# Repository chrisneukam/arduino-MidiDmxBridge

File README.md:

# Arduino Project: MIDI-DMX Bridge

The `MIDI-DMX Bridge` is an Arduino-based hardware and software solution that converts MIDI Continuous Controller signals to DMX commands. The project consists of a hardware schematic and PCB designed using KiCad, an Arduino sketch, and an Arduino library. It can be used to control DMX fixtures such as lights, fog machines, and more.

## Lightning Fixture Compatibility

The `MIDI-DMX Bridge` Arduino project is designed to seamlessly integrate with the lighting fixtures *Stairville CLB4 RGB Compact LED Bar 4* and two *Stairville LED Flood Panel 150*. Here's how the bridge supports these fixtures:

1. **Stairville CLB4 RGB Compact LED Bar 4**:
    - This LED bar operates in the 14-channel DMX mode, the start address 1.
    - Each of its four individual LED spots can be controlled independently using the MIDI-DMX Bridge.
    - Adjust colors, intensity, and effects with precision.
    - Perfect for creating dynamic lighting displays in various settings.

2. **Stairville LED Flood Panel 150**:
    - The LED Flood Panel operates in the 4-channel DMX mode, the start addresses are 15 and 19.
    - Use the MIDI-DMX Bridge to orchestrate its 150 LEDs for wide-area illumination.
    - Whether it’s stage lighting, architectural displays, or events, this panel delivers impressive results.

Remember to consult the user manuals for both fixtures to configure the MIDI-DMX Bridge effectively. Enjoy your creative lighting setups! 🌟

## Hardware Schematic

The hardware schematic for this project was designed using KiCad. The schematic includes the following components:

- **MIDI Input**: This component receives MIDI Continuous Controller signals on a defined MIDI channel from an external device.
- **Arduino Board**: This component processes the incoming MIDI signals and generates DMX commands.
- **DMX Output**: This component sends DMX commands to an external DMX device.
- **Potentiometer**: This component allows the user to adjust the intensity of the DMX signal.
- **Hardware Switch**: This component allows the user to select either a predefined DMX scene or the MIDI controlled dynamic scene.

The DMX circuit is based on the `DMX shield` from Matthias Hertel, see [DMX Shield for Arduino with isolation](https://www.mathertel.de/Arduino/DMXShield.aspx).

## PCB Design of the MIDI-DMX Bridge

The hardware design focuses on efficiency and space-saving. The compact printed circuit board (PCB) houses all essential components, including the Arduino ProMini microcontroller, MIDI interface, and DMX driver.

The PCB has the following features:

- A MIDI input jack that accepts standard 5-pin DIN connectors
- A MIDI through jack that accepts standard 5-pin DIN connectors
- A DMX output jack that supports both 3-pin XLR connectors
- A power jack that provides 9V DC power
- A Switch that selects between two DMX modes: static and dynamic scene
- A potentiometer that adjusts the DMX signal strength

The PCB layout and the circuit diagram as a 3D simulation, before and after final assembly, are shown below:

The PCB can be ordered from any PCB manufacturer that supports the KiCad format. Alternatively, the [Interactive BOM](./kicad/bom/ibom.html) tool can help with the assembly of the PCB.

The PCB shown was manufactured by [JLCPCB](https://jlcpcb.com/), the production data can be found in [kicad\production](./kicad/production) as a reference.

## Arduino Sketch

The Arduino sketch for this project is responsible for processing the incoming MIDI signals and generating DMX commands. The sketch uses its own implementation to receive MIDI signals and the [DMXSerial Library](https://github.com/mathertel/DMXSerial) to send DMX commands.

```c++
#include <DMXSerial.h>
#include <MidiDmxBridge.h>

static void onDmxChange(const uint8_t channel, const uint8_t value) {
  DMXSerial.write(channel, value);
}

static SerialReaderDefault reader;
static MidiDmxBridge MDXBridge(kMidiChannel, onDmxChange, reader);

void setup() {
  DMXSerial.init(DMXController);
  MDXBridge.begin();
}

void loop() {
  MDXBridge.setAttenuation(analogRead(kSensorPin));
  MDXBridge.listen();
}
```

For the complete Arduino sketch, please refer to [arduino-MidiDmxBridge.ino](./src/arduino-MidiDmxBridge/arduino-MidiDmxBridge.ino).

## Arduino Library

The Arduino library for this project is a custom library that provides additional functionality for processing MIDI signals and generating DMX commands. It is also available as [MidiDmxBridge](https://reference.arduino.cc/reference/en/libraries/mididmxbridge/) via the [Arduino Library manager](https://docs.arduino.cc/software/ide-v1/tutorials/installing-libraries/).
The library includes the following functions:

- `void begin()`: This function processes initializes the library.
- `void setStaticScene(const DmxRgbChannels& channels, const DmxRgb& rgb)`: This function defines the DMX static scene
- `void setAttenuation(const uint16_t attenuation)`: This function switches to the MIDI controlled dynamic scene.
- `void switchToDynamicScene()`: This function sets the attenuation of the generated DMX signal.
- `void switchToStaticScene()`: This function switches to the predefined static scene.
- `void listen()`: This function listens on the serial interface for the next MIDI CC value and updates the DMX state.

```c++
class MidiDmxBridge {
public:
  MidiDmxBridge(const uint8_t channel, DmxOnChangeCallback callback, ISerialReader& serial);
  void begin();
  void setStaticScene(const DmxRgbChannels& channels, const DmxRgb& rgb);
  void setAttenuation(const uint16_t attenuation);
  void switchToDynamicScene();
  void switchToStaticScene();
  void listen();
};
```

For the complete API, please refer to [MidiDmxBridge.h](./src/arduino-library/MidiDmxBridge/src/MidiDmxBridge.h).

### C++ Library development

The Arduino library is developed in C++ and uses CMake for configuration. The library is tested using gtest and documented using Doxygen.

```shell
cmake -S ./src/arduino-library/ -B ./build
cmake --build ./build
ctest --test-dir ./build/
```

On Linux OS code coverage using lcov and gcov is available:

```shell
cmake -DENABLE_COVERAGE=ON -S ./src/arduino-library/ -B ./build
cmake --build ./build
ctest --test-dir ./build/
cmake --build ./build --target coverage
```

The software documentation can then be accessed at [./build/html/index.html](./build/html/index.html), the code coverage results at [./build/coverage/index.html](./build/coverage/index.html).

## How to Run Codespell

To run [codespell](https://github.com/codespell-project/codespell), you need to have Python 3 installed on your system. You can install Python 3 from the official website: https://www.python.org/downloads/.

Once you have Python 3 installed, you can install [codespell](https://github.com/codespell-project/codespell) using pip, the Python package manager. Open a terminal or command prompt and type the following command:

```bash
pip install codespell
```

This will install [codespell](https://github.com/codespell-project/codespell) and all its dependencies.

To run [codespell](https://github.com/codespell-project/codespell), navigate to the root directory of your project in the terminal or command prompt and type the following command:

```bash
codespell
```

This will run [codespell](https://github.com/codespell-project/codespell) on all the files in the current directory and its subdirectories. [codespell](https://github.com/codespell-project/codespell) will check for common misspellings and suggest corrections. You can use the `-w` option to write the changes directly to the files.

```bash
codespell -w
```

For more information on how to use [codespell](https://github.com/codespell-project/codespell), including a list of all the available options, please refer to the official documentation: https://github.com/codespell-project/codespell#usage.

## Generating a Source Code Release Package with CPack

CPack is a powerful tool that allows to create binary installers and source packages. To generate a source code release package, use the following commands:

```bash
cd ./build
cpack --config CPackSourceConfig.cmake
```

This will create a source package in the CMake build directory.

## Conclusion

This project provides a simple and effective solution for converting MIDI Continuous Controller signals to DMX commands. The hardware schematic, Arduino sketch, and Arduino library can be easily modified to suit your specific needs. If you have any questions or comments about this project, please feel free to contact me.

## License

This library and the PCB design are released under the Apache V2.0 License. See [LICENSE](./LICENSE) for more information.

Please let me know if you have any questions or feedback. I'm happy to help! 😊🎵

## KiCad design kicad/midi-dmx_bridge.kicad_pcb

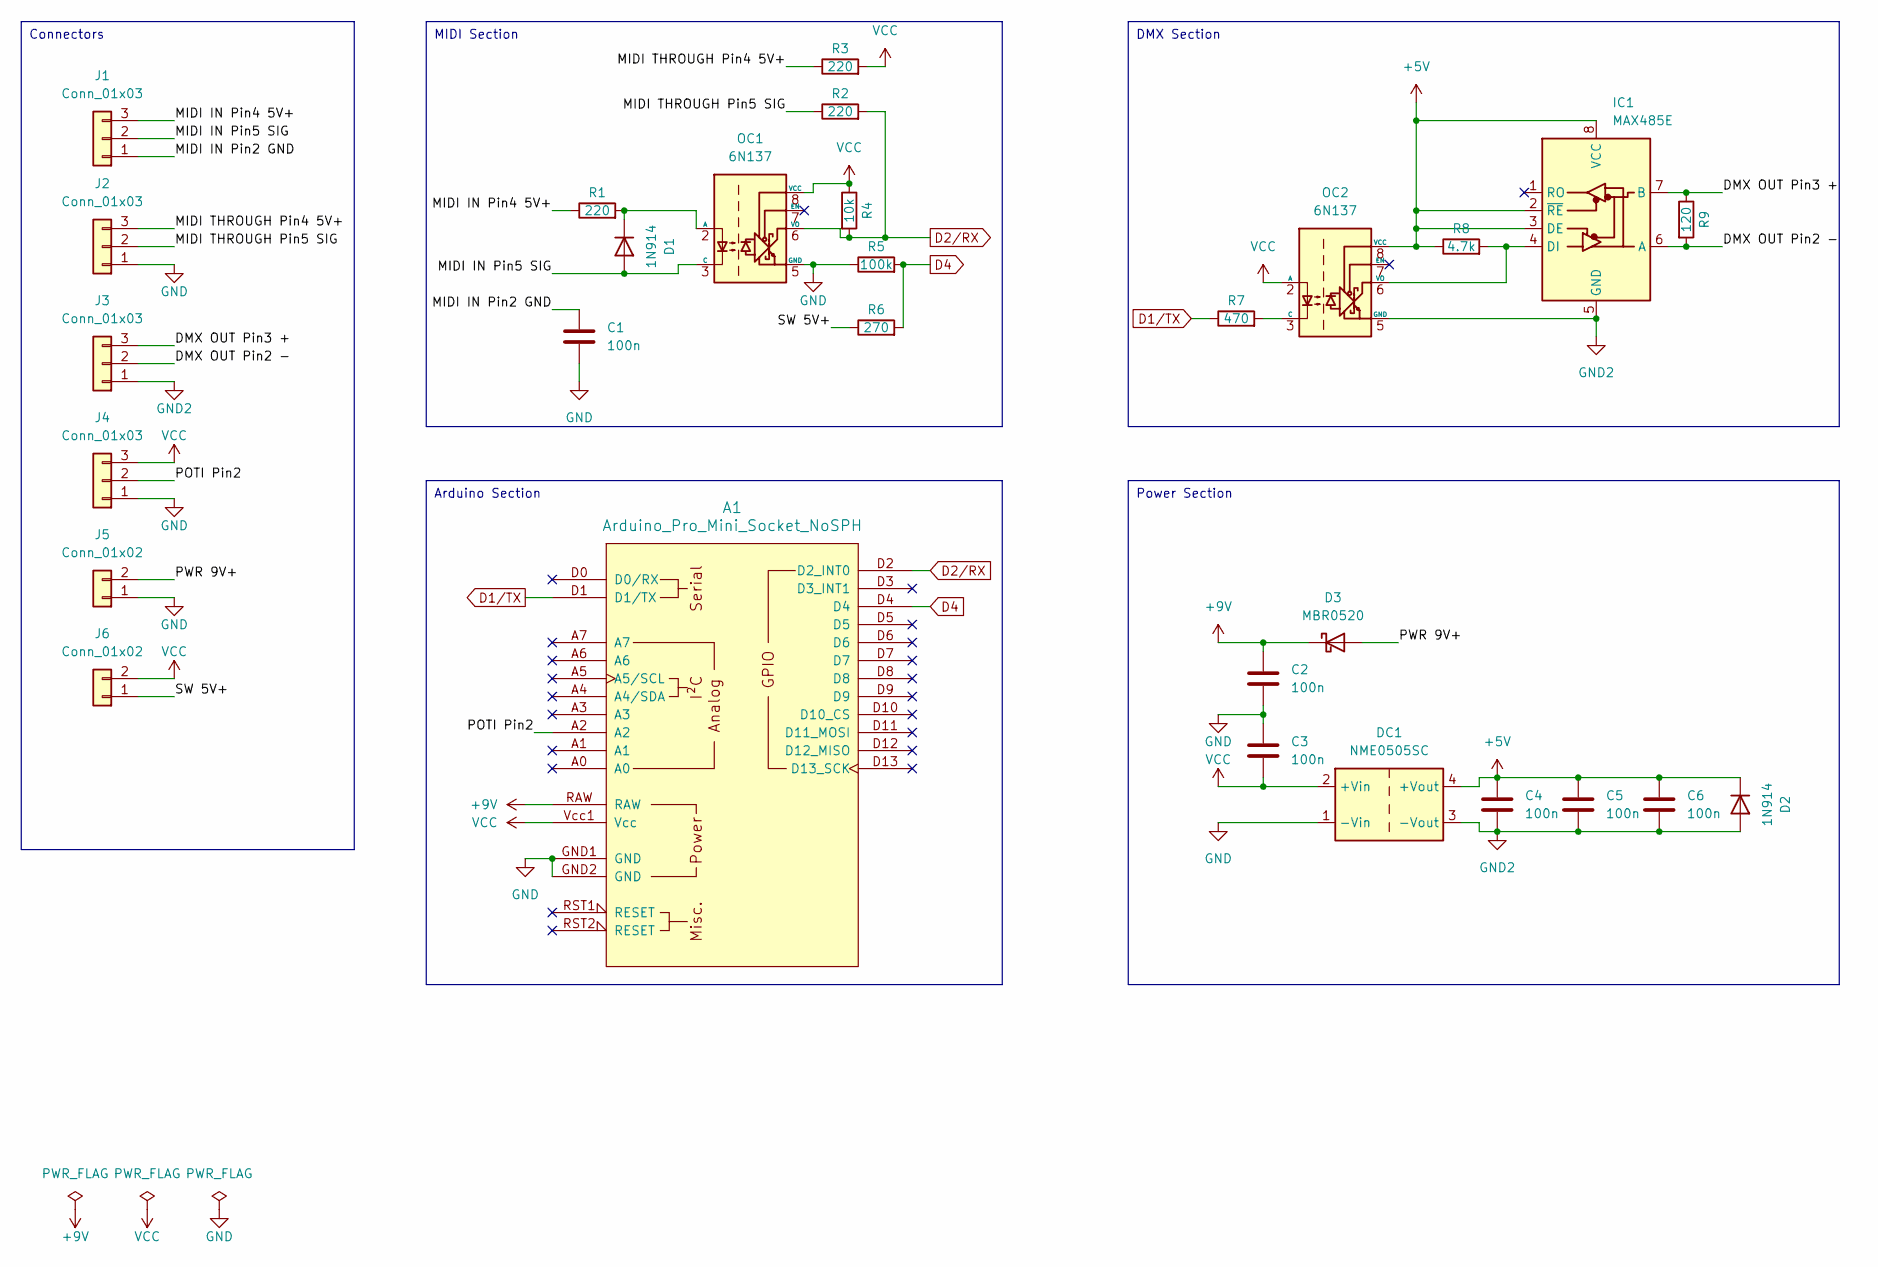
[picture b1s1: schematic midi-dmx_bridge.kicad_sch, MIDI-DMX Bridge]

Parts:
A1: Arduino_Pro_Mini_Socket_NoSPH
C1, C2, C3, C4, C5, C6: 100n; C_1206_3216Metric
D1, D2: 1N914; D_SOD-123
D3: MBR0520; D_SOD-123
DC1: NME0505SC; Converter_DCDC_Murata_MEE1SxxxxSC_THT
IC1: MAX485E; SOIC-8_3.9x4.9mm_P1.27mm
J1, J2, J3, J4: Conn_01x03; Molex_KK-254_AE-6410-03A_1x03_P2.54mm_Vertical
J5, J6: Conn_01x02; Molex_KK-254_AE-6410-02A_1x02_P2.54mm_Vertical
OC1, OC2: 6N137; SMDIP-8_W9.53mm
R1, R2, R3: 220; R_1206_3216Metric
R4: 10k; R_1206_3216Metric
R5: 100k; R_1206_3216Metric
R6: 270; R_1206_3216Metric
R7: 470; R_1206_3216Metric
R8: 4.7k; R_1206_3216Metric
R9: 120; R_1206_3216Metric

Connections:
+5V: C4.1, C5.1, C6.1, D2.1 (K), DC1.4 (+Vout), IC1.2 (~RE), IC1.3 (DE), IC1.8 (VCC), OC2.8 (VCC), R8.1
+9V: A1.RAW, C2.1, D3.1 (K)
/DMX OUT Pin2 -: IC1.6 (A), J3.2, R9.2
/DMX OUT Pin3 +: IC1.7 (B), J3.3, R9.1
/MIDI IN Pin2 GND: C1.1, J1.1
/MIDI IN Pin4 5V+: J1.3, R1.1
/MIDI IN Pin5 SIG: D1.2 (A), J1.2, OC1.3 (C)
/MIDI THROUGH Pin4 5V+: J2.3, R3.1
/MIDI THROUGH Pin5 SIG: J2.2, R2.1
/POTI Pin2: A1.A2, J4.2
/PWR 9V+: D3.2 (A), J5.2
/SW 5V+: J6.1, R6.1
D1/TX: A1.D1 (D1/TX), R7.1
D2/RX: A1.D2 (D2_INT0), OC1.6 (VO), R2.2, R4.2
D4: A1.D4, R5.2, R6.2
GND: A1.GND1 (GND), A1.GND2 (GND), C1.2, C2.2, C3.1, DC1.1 (-Vin), J2.1, J4.1, J5.1, OC1.5 (GND), R5.1
GND2: C4.2, C5.2, C6.2, D2.2 (A), DC1.3 (-Vout), IC1.5 (GND), J3.1, OC2.5 (GND)
unnamed: D1.1 (K), OC1.2 (A), R1.2
unnamed: IC1.4 (DI), OC2.6 (VO), R8.2
unnamed: OC2.3 (C), R7.2
VCC: A1.Vcc1 (Vcc), C3.2, DC1.2 (+Vin), J4.3, J6.2, OC1.8 (VCC), OC2.2 (A), R3.2, R4.1

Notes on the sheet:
DMX Section
Arduino Section
MIDI Section
Power Section
Connectors

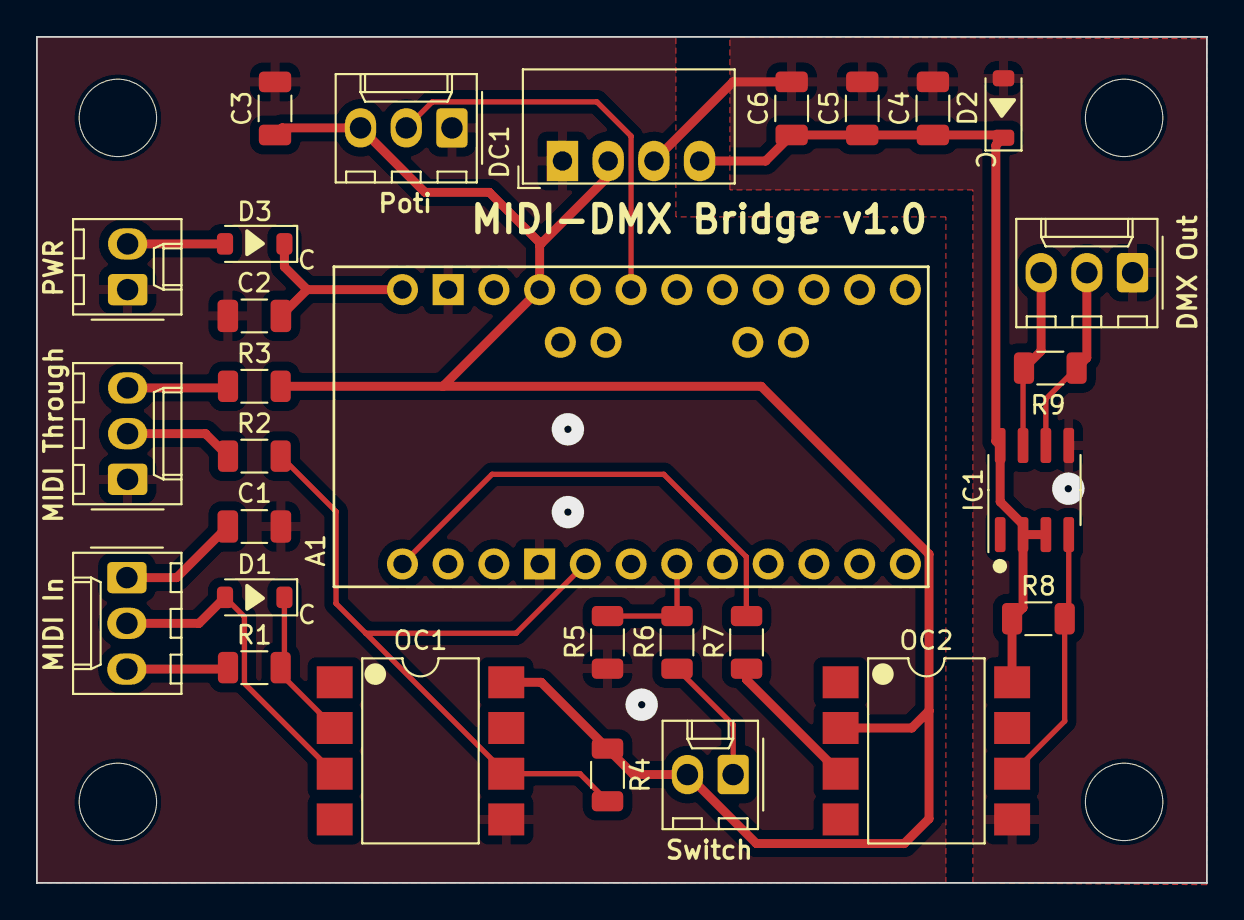
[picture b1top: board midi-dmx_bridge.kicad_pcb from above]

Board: 2 copper layers, 65.0 x 47.0 mm, 29 parts (0 on the bottom side), 21 nets.

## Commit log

2024-02-18 feat: MIDI-DMX Bridge
    This is the first fully functional version of the MIDI-DMX Bridge
    Arduino project. It consists of the MIDI-DMX Bridge schematic created
    in KiCad, the Arduino library developed in C++ and the Arduino sketch
    for the Arduino Pro Mini.
2024-02-18 feat: MIDI-DMX Bridge (#1)
    This is the first fully functional version of the MIDI-DMX Bridge
    Arduino project. It consists of the MIDI-DMX Bridge schematic created
    in KiCad, the Arduino library developed in C++ and the Arduino sketch
    for the Arduino Pro Mini.
2024-02-25 feat: Dimmer Support
    In addition to the RGB channels, this feature also takes into account the dimmers of the lighting fixtures.
    Full support of Stairville CLB4 RGB Compact LED Bar 4 and Stairville LED Flood Panel 150.

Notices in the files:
README.md:
License: Apache 2.0
